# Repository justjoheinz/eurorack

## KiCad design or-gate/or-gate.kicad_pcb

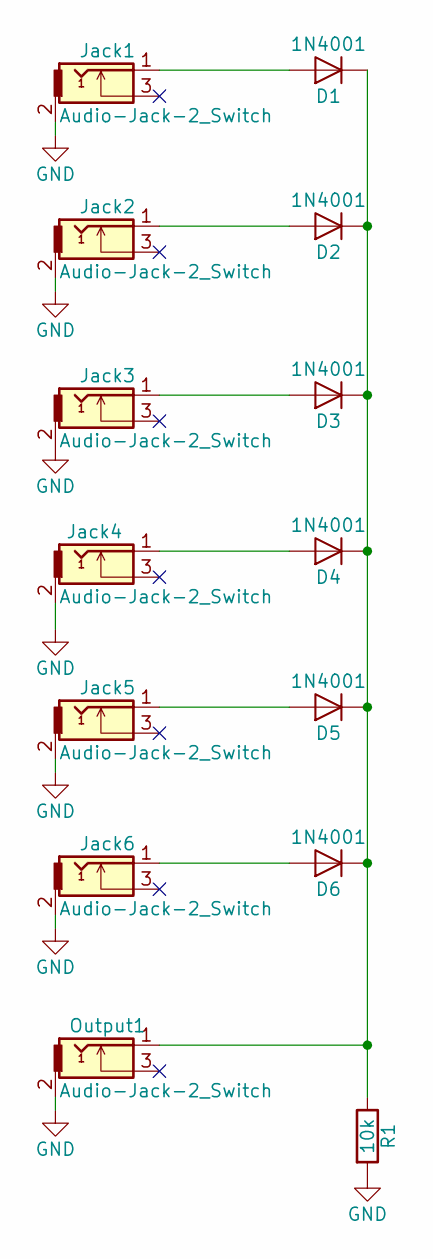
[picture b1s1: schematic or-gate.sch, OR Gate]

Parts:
D1, D2: 1N4001; D_DO-41_SOD81_P7.62mm_Horizontal
D3, D4, D5, D6: 1N4001; LED_D5.0mm
Jack1, Jack2, Jack3, Jack4, Jack5, Jack6: Audio-Jack-2_Switch; PJ301M-12
Output1: Audio-Jack-2_Switch; PJ301M-12
R1: 10k; R_Axial_DIN0204_L3.6mm_D1.6mm_P7.62mm_Horizontal

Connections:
GND: Jack1.2, Jack2.2, Jack3.2, Jack4.2, Jack5.2, Jack6.2, Output1.2, R1.2
unnamed: D1.1 (K), D2.1 (K), D3.1 (K), D4.1 (K), D5.1 (K), D6.1 (K), Output1.1, R1.1
unnamed: D1.2 (A), Jack1.1
unnamed: D2.2 (A), Jack2.1
unnamed: D3.2 (A), Jack3.1
unnamed: D4.2 (A), Jack4.1
unnamed: D5.2 (A), Jack5.1
unnamed: D6.2 (A), Jack6.1

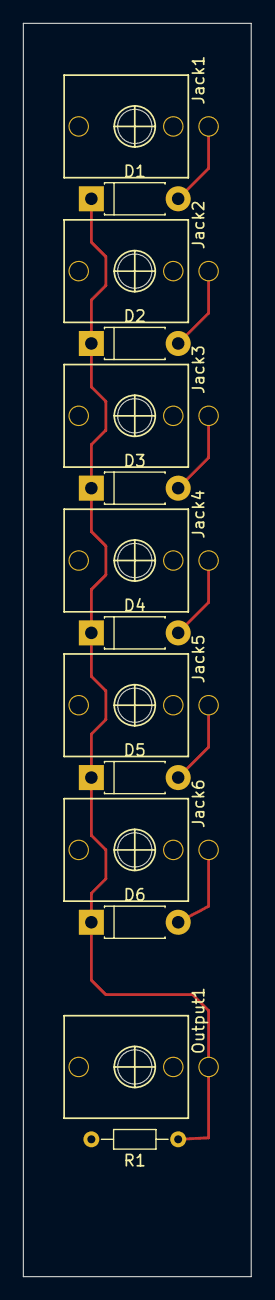
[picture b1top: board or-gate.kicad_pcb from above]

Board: 2 copper layers, 20.0 x 110.0 mm, 14 parts (0 on the bottom side), 8 nets.

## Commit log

2017-09-22 initial version
